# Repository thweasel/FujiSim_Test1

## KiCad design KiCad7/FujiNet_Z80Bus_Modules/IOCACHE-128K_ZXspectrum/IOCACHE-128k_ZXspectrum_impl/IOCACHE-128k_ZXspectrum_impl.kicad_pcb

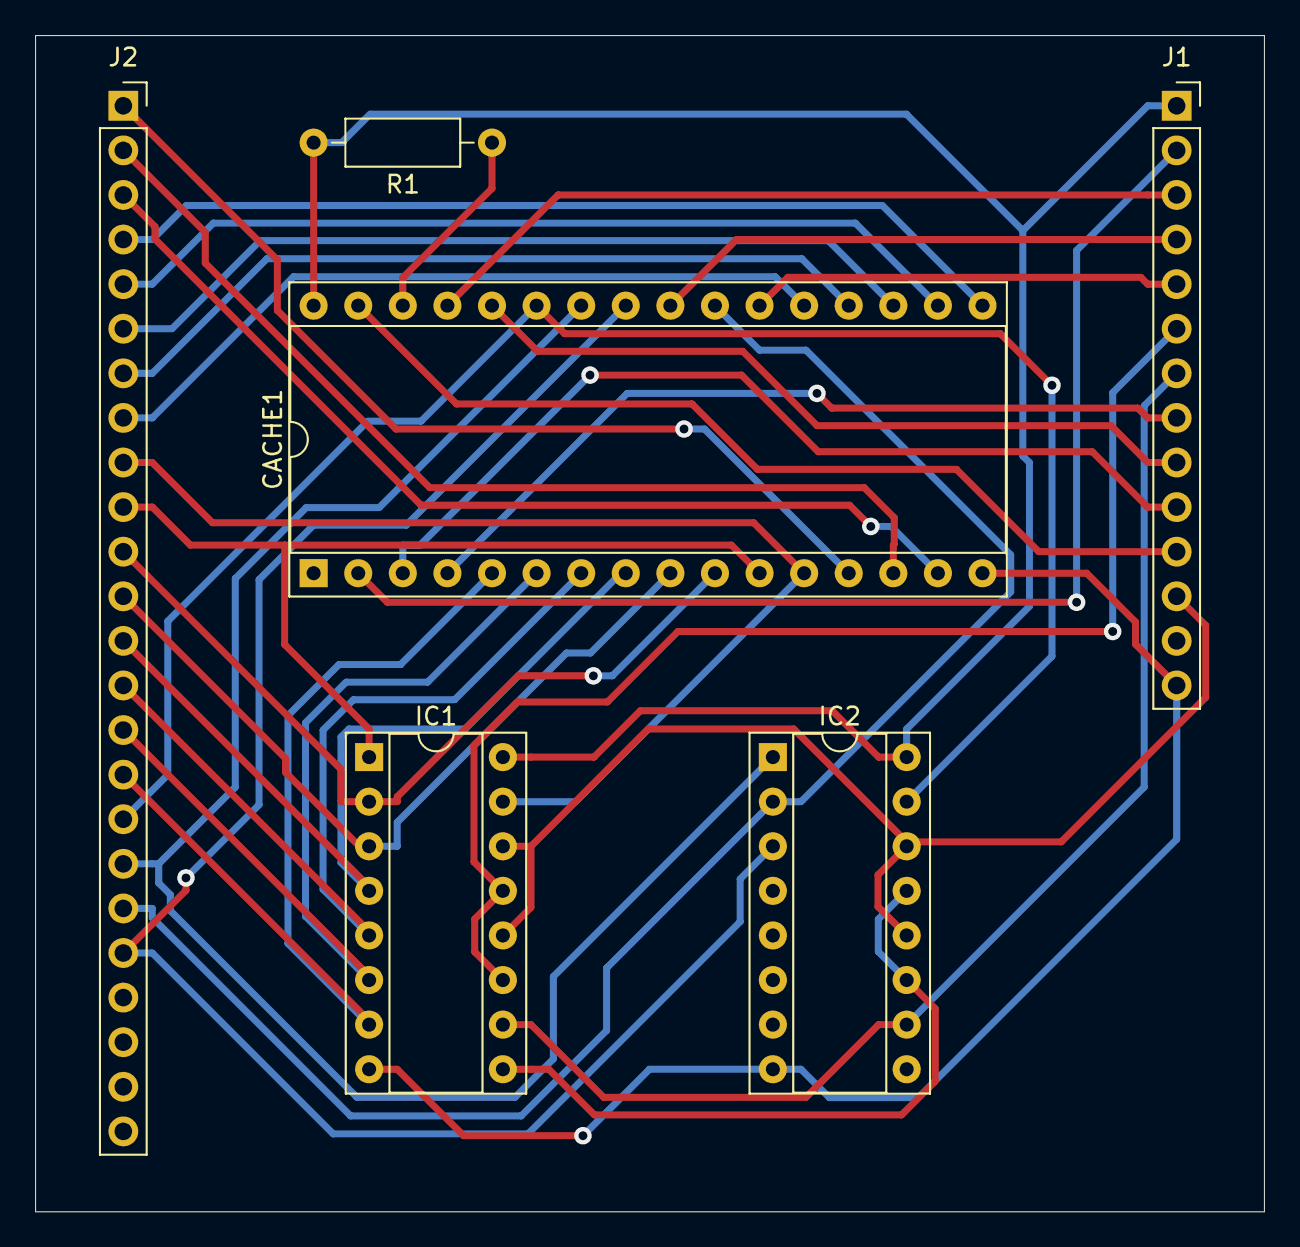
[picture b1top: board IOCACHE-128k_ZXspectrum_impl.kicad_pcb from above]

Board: 2 copper layers, 70.0 x 67.0 mm, 6 parts (0 on the bottom side), 35 nets.

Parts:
CACHE1: AS6C1008-55PCN; DIP-32_W15.24mm_Socket
IC1, IC2: 74HC590N; DIP-16_W7.62mm_Socket
J1: Conn_01x14_Socket; PinSocket_1x14_P2.54mm_Vertical
J2: Conn_01x24_Socket; PinSocket_1x24_P2.54mm_Vertical
R1: 10K; R_Axial_DIN0207_L6.3mm_D2.5mm_P10.16mm_Horizontal

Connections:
+5V: CACHE1.32 (VCC), IC1.16 (VCC), IC2.16 (VCC), J1.1, R1.2
/IOCACHE-128K_ZXspectrum/CACHE_CE2: CACHE1.30 (CE2#), R1.1
/IOCACHE-128K_ZXspectrum/CACHE_CONTROL.A16: CACHE1.2 (A16), J1.2
/IOCACHE-128K_ZXspectrum/CACHE_CONTROL.CS: CACHE1.22 (CE#), J1.5
/IOCACHE-128K_ZXspectrum/CACHE_CONTROL.DATASTATUS+PERM_Z80_IORQ: IC1.11 (CPC), IC1.13 (CPR), J1.6
/IOCACHE-128K_ZXspectrum/CACHE_CONTROL.OE: CACHE1.24 (OE#), J1.4
/IOCACHE-128K_ZXspectrum/CACHE_CONTROL.WE: CACHE1.29 (WE#), J1.3
/IOCACHE-128K_ZXspectrum/CACHE_DATASTATUS: IC1.12 (~CE), IC1.14 (~OE), IC2.12 (~CE), IC2.14 (~OE), J1.12
/IOCACHE-128K_ZXspectrum/CACHE_SEL_0: CACHE1.4 (A12), J1.8
/IOCACHE-128K_ZXspectrum/CACHE_SEL_1: CACHE1.28 (A13), J1.9
/IOCACHE-128K_ZXspectrum/CACHE_SEL_2: CACHE1.3 (A14), J1.10
/IOCACHE-128K_ZXspectrum/CACHE_SEL_3: CACHE1.31 (A15), J1.11
/IOCACHE-128K_ZXspectrum/LOCAL_A0: CACHE1.12 (A0), IC1.15 (Q0), J2.9
/IOCACHE-128K_ZXspectrum/LOCAL_A1: CACHE1.11 (A1), IC1.1 (Q1), J2.10
/IOCACHE-128K_ZXspectrum/LOCAL_A2: CACHE1.10 (A2), IC1.2 (Q2), J2.11
/IOCACHE-128K_ZXspectrum/LOCAL_A3: CACHE1.9 (A3), IC1.3 (Q3), J2.12
/IOCACHE-128K_ZXspectrum/LOCAL_A4: CACHE1.8 (A4), IC1.4 (Q4), J2.13
/IOCACHE-128K_ZXspectrum/LOCAL_A5: CACHE1.7 (A5), IC1.5 (Q5), J2.14
/IOCACHE-128K_ZXspectrum/LOCAL_A6: CACHE1.6 (A6), IC1.6 (Q6), J2.15
/IOCACHE-128K_ZXspectrum/LOCAL_A7: CACHE1.5 (A7), IC1.7 (Q7), J2.16
/IOCACHE-128K_ZXspectrum/LOCAL_A8: CACHE1.27 (A8), IC2.15 (Q0), J2.17
/IOCACHE-128K_ZXspectrum/LOCAL_A9: CACHE1.26 (A9), IC2.1 (Q1), J2.18
/IOCACHE-128K_ZXspectrum/LOCAL_A10: CACHE1.23 (A10), IC2.2 (Q2), J2.19
/IOCACHE-128K_ZXspectrum/LOCAL_A11: CACHE1.25 (A11), IC2.3 (Q3), J2.20
/IOCACHE-128K_ZXspectrum/LOCAL_D0: CACHE1.13 (DQ0), J2.1
/IOCACHE-128K_ZXspectrum/LOCAL_D1: CACHE1.14 (DQ1), J2.2
/IOCACHE-128K_ZXspectrum/LOCAL_D2: CACHE1.15 (DQ2), J2.3
/IOCACHE-128K_ZXspectrum/LOCAL_D3: CACHE1.17 (DQ3), J2.4
/IOCACHE-128K_ZXspectrum/LOCAL_D4: CACHE1.18 (DQ4), J2.5
/IOCACHE-128K_ZXspectrum/LOCAL_D5: CACHE1.19 (DQ5), J2.6
/IOCACHE-128K_ZXspectrum/LOCAL_D6: CACHE1.20 (DQ6), J2.7
/IOCACHE-128K_ZXspectrum/LOCAL_D7: CACHE1.21 (DQ7), J2.8
/IOCACHE-128K_ZXspectrum/Z80_HARDLOCK: IC1.10 (~MRC), IC2.10 (~MRC), J1.7
GND: CACHE1.16 (VSS), IC1.8 (GND), IC2.8 (GND), J1.14
unnamed: IC1.9 (~RCO), IC2.11 (CPC), IC2.13 (CPR)

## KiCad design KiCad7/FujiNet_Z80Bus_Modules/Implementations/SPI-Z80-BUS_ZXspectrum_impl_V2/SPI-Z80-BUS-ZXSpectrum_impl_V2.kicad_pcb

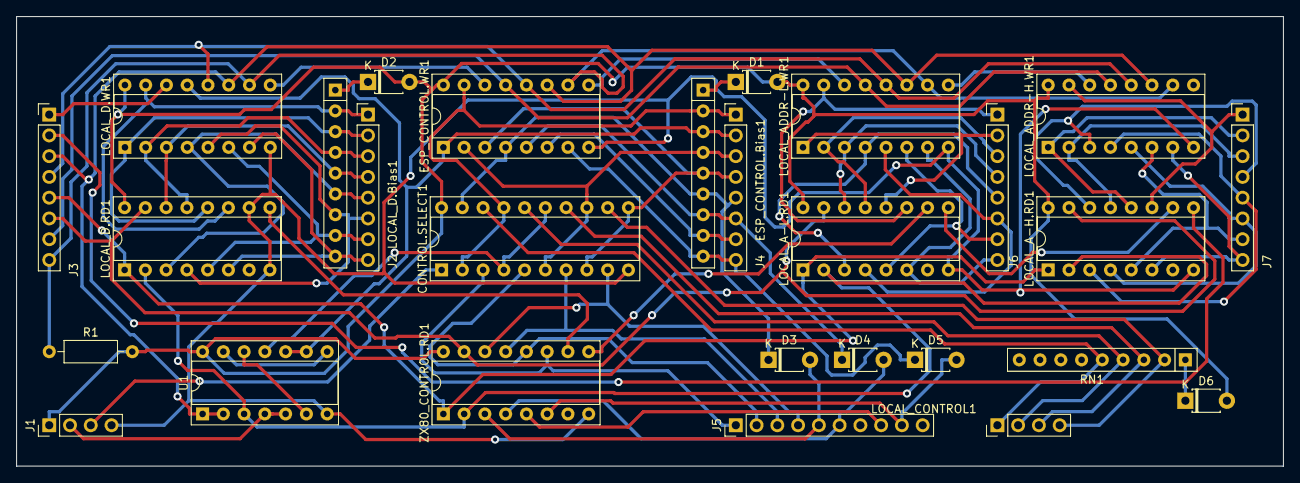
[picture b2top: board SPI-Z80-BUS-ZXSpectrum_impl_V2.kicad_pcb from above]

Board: 2 copper layers, 155.0 x 55.0 mm, 28 parts (0 on the bottom side), 69 nets.

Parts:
CONTROL.SELECT1: 74HC244N; DIP-20_W7.62mm_Socket
D1, D2, D3, D4, D5, D6: 1N4148; D_T-1_P5.08mm_Horizontal
ESP_CONTROL.Bias1: 4609M-101-103LF; R_Array_SIP9
ESP_CONTROL.WR1: 74595N; DIP-16_W7.62mm_Socket
J1: PinHeader_2.54mm; PinHeader_1x04_P2.54mm_Vertical
J2: LOCAL_D; PinHeader_1x08_P2.54mm_Vertical
J3: ESP_SPI_INT; PinHeader_1x08_P2.54mm_Vertical
J4: ESP_CONTROL; PinHeader_1x08_P2.54mm_Vertical
J5: Z80_CONTROL; PinHeader_1x10_P2.54mm_Vertical
J6: LOCAL_A-L; PinHeader_1x08_P2.54mm_Vertical
J7: LOCAL_A-H; PinHeader_1x08_P2.54mm_Vertical
LOCAL_A-H.RD1: 74HC165N; DIP-16_W7.62mm_Socket
LOCAL_A-L.RD1: 74HC165N; DIP-16_W7.62mm_Socket
LOCAL_ADDR-H.WR1: 74595N; DIP-16_W7.62mm_Socket
LOCAL_ADDR-L.WR1: 74595N; DIP-16_W7.62mm_Socket
LOCAL_CONTROL1: LOCAL_CONTROL; PinHeader_1x04_P2.54mm_Vertical
LOCAL_D.Bias1: 4609M-101-103LF; R_Array_SIP9
LOCAL_D.RD1: 74HC165N; DIP-16_W7.62mm_Socket
LOCAL_D.WR1: 74595N; DIP-16_W7.62mm_Socket
R1: 22K; R_Axial_DIN0207_L6.3mm_D2.5mm_P10.16mm_Horizontal
RN1: LOCAL_CONTROL.Bias; R_Array_SIP9
U1: 74HC00; DIP-14_W7.62mm_Socket
ZX80_CONTROL.RD1: 74HC165N; DIP-16_W7.62mm_Socket

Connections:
+5V: CONTROL.SELECT1.20 (VCC), D1.2 (A), D2.2 (A), D6.2 (A), ESP_CONTROL.WR1.16 (VCC), J1.1, LOCAL_A-H.RD1.16 (VCC), LOCAL_A-L.RD1.16 (VCC), LOCAL_ADDR-H.WR1.16 (VCC), LOCAL_ADDR-L.WR1.16 (VCC), LOCAL_D.RD1.16 (VCC), LOCAL_D.WR1.16 (VCC), R1.2, U1.14 (VCC), ZX80_CONTROL.RD1.16 (VCC)
/SPI-Z80-BUS/!ESP_HARDLOCK: CONTROL.SELECT1.1 (1OE), J1.3
/SPI-Z80-BUS/ESP_CONTROL.BUSRQ: CONTROL.SELECT1.19 (2OE), D3.1 (K), ESP_CONTROL.Bias1.6 (R5), ESP_CONTROL.WR1.4 (QE), J4.5
/SPI-Z80-BUS/ESP_CONTROL.IORQ: CONTROL.SELECT1.6 (1A2), CONTROL.SELECT1.13 (2A2), ESP_CONTROL.Bias1.4 (R3), ESP_CONTROL.WR1.2 (QC), J4.3
/SPI-Z80-BUS/ESP_CONTROL.MEMRQ: CONTROL.SELECT1.8 (1A3), CONTROL.SELECT1.11 (2A3), ESP_CONTROL.Bias1.5 (R4), ESP_CONTROL.WR1.3 (QD), J4.4
/SPI-Z80-BUS/ESP_CONTROL.NMI: D5.1 (K), ESP_CONTROL.Bias1.9 (R8), ESP_CONTROL.WR1.7 (QH), J4.8
/SPI-Z80-BUS/ESP_CONTROL.RD: CONTROL.SELECT1.2 (1A0), CONTROL.SELECT1.17 (2A0), ESP_CONTROL.Bias1.2 (R1), ESP_CONTROL.WR1.15 (QA), J4.1
/SPI-Z80-BUS/ESP_CONTROL.ROMCS: ESP_CONTROL.Bias1.8 (R7), ESP_CONTROL.WR1.6 (QG), J4.7
/SPI-Z80-BUS/ESP_CONTROL.WAIT: D4.1 (K), ESP_CONTROL.Bias1.7 (R6), ESP_CONTROL.WR1.5 (QF), J4.6
/SPI-Z80-BUS/ESP_CONTROL.WR: ESP_CONTROL.Bias1.3 (R2), ESP_CONTROL.WR1.1 (QB), J4.2, LOCAL_D.WR1.13 (~OE), U1.9, U1.10
/SPI-Z80-BUS/ESP_PULSE: J1.2, U1.4, U1.5
/SPI-Z80-BUS/ESP_SPI_INT.CE: J3.6, LOCAL_A-H.RD1.15 (~CE), LOCAL_A-L.RD1.15 (~CE), LOCAL_D.RD1.15 (~CE), ZX80_CONTROL.RD1.15 (~CE)
/SPI-Z80-BUS/ESP_SPI_INT.MISO: J3.2, LOCAL_A-H.RD1.9 (Q7)
/SPI-Z80-BUS/ESP_SPI_INT.MOSI: J3.1, LOCAL_D.WR1.14 (SER)
/SPI-Z80-BUS/ESP_SPI_INT.MR: ESP_CONTROL.WR1.10 (~SRCLR), J3.8, LOCAL_ADDR-H.WR1.10 (~SRCLR), LOCAL_ADDR-L.WR1.10 (~SRCLR), LOCAL_D.WR1.10 (~SRCLR), R1.1
/SPI-Z80-BUS/ESP_SPI_INT.OE: ESP_CONTROL.WR1.13 (~OE), J3.7, LOCAL_ADDR-H.WR1.13 (~OE), LOCAL_ADDR-L.WR1.13 (~OE)
/SPI-Z80-BUS/ESP_SPI_INT.PL: J3.5, LOCAL_A-H.RD1.1 (~PL), LOCAL_A-L.RD1.1 (~PL), LOCAL_D.RD1.1 (~PL), ZX80_CONTROL.RD1.1 (~PL)
/SPI-Z80-BUS/ESP_SPI_INT.SCK: ESP_CONTROL.WR1.11 (SRCLK), J3.3, LOCAL_ADDR-H.WR1.11 (SRCLK), LOCAL_ADDR-L.WR1.11 (SRCLK), LOCAL_D.WR1.11 (SRCLK), U1.1, U1.2
/SPI-Z80-BUS/ESP_SPI_INT.STC: ESP_CONTROL.WR1.12 (RCLK), J3.4, LOCAL_ADDR-H.WR1.12 (RCLK), LOCAL_ADDR-L.WR1.12 (RCLK), LOCAL_D.WR1.12 (RCLK)
/SPI-Z80-BUS/LOCAL_A0: J6.1, LOCAL_A-L.RD1.11 (D0), LOCAL_ADDR-L.WR1.15 (QA)
/SPI-Z80-BUS/LOCAL_A1: J6.2, LOCAL_A-L.RD1.12 (D1), LOCAL_ADDR-L.WR1.1 (QB)
/SPI-Z80-BUS/LOCAL_A2: J6.3, LOCAL_A-L.RD1.13 (D2), LOCAL_ADDR-L.WR1.2 (QC)
/SPI-Z80-BUS/LOCAL_A3: J6.4, LOCAL_A-L.RD1.14 (D3), LOCAL_ADDR-L.WR1.3 (QD)
/SPI-Z80-BUS/LOCAL_A4: J6.5, LOCAL_A-L.RD1.3 (D4), LOCAL_ADDR-L.WR1.4 (QE)
/SPI-Z80-BUS/LOCAL_A5: J6.6, LOCAL_A-L.RD1.4 (D5), LOCAL_ADDR-L.WR1.5 (QF)
/SPI-Z80-BUS/LOCAL_A6: J6.7, LOCAL_A-L.RD1.5 (D6), LOCAL_ADDR-L.WR1.6 (QG)
/SPI-Z80-BUS/LOCAL_A7: J6.8, LOCAL_A-L.RD1.6 (D7), LOCAL_ADDR-L.WR1.7 (QH)
/SPI-Z80-BUS/LOCAL_A8: J7.1, LOCAL_A-H.RD1.11 (D0), LOCAL_ADDR-H.WR1.15 (QA)
/SPI-Z80-BUS/LOCAL_A9: J7.2, LOCAL_A-H.RD1.12 (D1), LOCAL_ADDR-H.WR1.1 (QB)
/SPI-Z80-BUS/LOCAL_A10: J7.3, LOCAL_A-H.RD1.13 (D2), LOCAL_ADDR-H.WR1.2 (QC)
/SPI-Z80-BUS/LOCAL_A11: J7.4, LOCAL_A-H.RD1.14 (D3), LOCAL_ADDR-H.WR1.3 (QD)
/SPI-Z80-BUS/LOCAL_A12: J7.5, LOCAL_A-H.RD1.3 (D4), LOCAL_ADDR-H.WR1.4 (QE)
/SPI-Z80-BUS/LOCAL_A13: J7.6, LOCAL_A-H.RD1.4 (D5), LOCAL_ADDR-H.WR1.5 (QF)
/SPI-Z80-BUS/LOCAL_A14: J7.7, LOCAL_A-H.RD1.5 (D6), LOCAL_ADDR-H.WR1.6 (QG)
/SPI-Z80-BUS/LOCAL_A15: J7.8, LOCAL_A-H.RD1.6 (D7), LOCAL_ADDR-H.WR1.7 (QH)
/SPI-Z80-BUS/LOCAL_CONTROL.IORQ: CONTROL.SELECT1.14 (1Y2), LOCAL_CONTROL1.3, RN1.3 (R2)
/SPI-Z80-BUS/LOCAL_CONTROL.MEMRQ: CONTROL.SELECT1.12 (1Y3), LOCAL_CONTROL1.4, RN1.2 (R1)
/SPI-Z80-BUS/LOCAL_CONTROL.RD: CONTROL.SELECT1.18 (1Y0), LOCAL_CONTROL1.1, RN1.5 (R4)
/SPI-Z80-BUS/LOCAL_CONTROL.WR: CONTROL.SELECT1.16 (1Y1), LOCAL_CONTROL1.2, RN1.4 (R3)
/SPI-Z80-BUS/LOCAL_D0: J2.1, LOCAL_D.Bias1.2 (R1), LOCAL_D.RD1.11 (D0), LOCAL_D.WR1.15 (QA)
/SPI-Z80-BUS/LOCAL_D1: J2.2, LOCAL_D.Bias1.3 (R2), LOCAL_D.RD1.12 (D1), LOCAL_D.WR1.1 (QB)
/SPI-Z80-BUS/LOCAL_D2: J2.3, LOCAL_D.Bias1.4 (R3), LOCAL_D.RD1.13 (D2), LOCAL_D.WR1.2 (QC)
/SPI-Z80-BUS/LOCAL_D3: J2.4, LOCAL_D.Bias1.5 (R4), LOCAL_D.RD1.14 (D3), LOCAL_D.WR1.3 (QD)
/SPI-Z80-BUS/LOCAL_D4: J2.5, LOCAL_D.Bias1.6 (R5), LOCAL_D.RD1.3 (D4), LOCAL_D.WR1.4 (QE)
/SPI-Z80-BUS/LOCAL_D5: J2.6, LOCAL_D.Bias1.7 (R6), LOCAL_D.RD1.4 (D5), LOCAL_D.WR1.5 (QF)
/SPI-Z80-BUS/LOCAL_D6: J2.7, LOCAL_D.Bias1.8 (R7), LOCAL_D.RD1.5 (D6), LOCAL_D.WR1.6 (QG)
/SPI-Z80-BUS/LOCAL_D7: J2.8, LOCAL_D.Bias1.9 (R8), LOCAL_D.RD1.6 (D7), LOCAL_D.WR1.7 (QH)
/SPI-Z80-BUS/SPI-Z80-BUS_read/ESP_SPI_INT.SCK: LOCAL_A-H.RD1.2 (CP), LOCAL_A-L.RD1.2 (CP), LOCAL_D.RD1.2 (CP), U1.3, ZX80_CONTROL.RD1.2 (CP)
/SPI-Z80-BUS/Z80_CONTROL.BUSACK: J5.8, ZX80_CONTROL.RD1.5 (D6)
/SPI-Z80-BUS/Z80_CONTROL.BUSRQ: D3.2 (A), J5.5, ZX80_CONTROL.RD1.3 (D4)
/SPI-Z80-BUS/Z80_CONTROL.IORQ: CONTROL.SELECT1.7 (2Y2), J5.3, ZX80_CONTROL.RD1.13 (D2)
/SPI-Z80-BUS/Z80_CONTROL.MEMRQ: CONTROL.SELECT1.9 (2Y3), J5.4, ZX80_CONTROL.RD1.14 (D3)
/SPI-Z80-BUS/Z80_CONTROL.NMI: D5.2 (A), J5.9, ZX80_CONTROL.RD1.6 (D7)
/SPI-Z80-BUS/Z80_CONTROL.RD: CONTROL.SELECT1.3 (2Y0), J5.1, ZX80_CONTROL.RD1.11 (D0)
/SPI-Z80-BUS/Z80_CONTROL.WAIT: D4.2 (A), J5.6, ZX80_CONTROL.RD1.4 (D5)
/SPI-Z80-BUS/Z80_CONTROL.WR: CONTROL.SELECT1.5 (2Y1), J5.2, ZX80_CONTROL.RD1.12 (D1)
GND: CONTROL.SELECT1.10 (GND), ESP_CONTROL.WR1.8 (GND), J1.4, LOCAL_A-H.RD1.8 (GND), LOCAL_A-L.RD1.8 (GND), LOCAL_ADDR-H.WR1.8 (GND), LOCAL_ADDR-L.WR1.8 (GND), LOCAL_D.RD1.8 (GND), LOCAL_D.RD1.10 (DS), LOCAL_D.WR1.8 (GND), U1.7 (GND), ZX80_CONTROL.RD1.8 (GND)
unnamed: CONTROL.SELECT1.4 (1A1), CONTROL.SELECT1.15 (2A1), U1.11
unnamed: D1.1 (K), ESP_CONTROL.Bias1.1 (common)
unnamed: D2.1 (K), LOCAL_D.Bias1.1 (common)
unnamed: D6.1 (K), RN1.1 (common)
unnamed: ESP_CONTROL.WR1.9 (QH'), LOCAL_ADDR-L.WR1.14 (SER)
unnamed: ESP_CONTROL.WR1.14 (SER), LOCAL_D.WR1.9 (QH')
unnamed: LOCAL_A-H.RD1.10 (DS), LOCAL_A-L.RD1.9 (Q7)
unnamed: LOCAL_A-L.RD1.10 (DS), ZX80_CONTROL.RD1.9 (Q7)
unnamed: LOCAL_ADDR-H.WR1.14 (SER), LOCAL_ADDR-L.WR1.9 (QH')
unnamed: LOCAL_D.RD1.9 (Q7), ZX80_CONTROL.RD1.10 (DS)
unnamed: U1.6, U1.12
unnamed: U1.8, U1.13

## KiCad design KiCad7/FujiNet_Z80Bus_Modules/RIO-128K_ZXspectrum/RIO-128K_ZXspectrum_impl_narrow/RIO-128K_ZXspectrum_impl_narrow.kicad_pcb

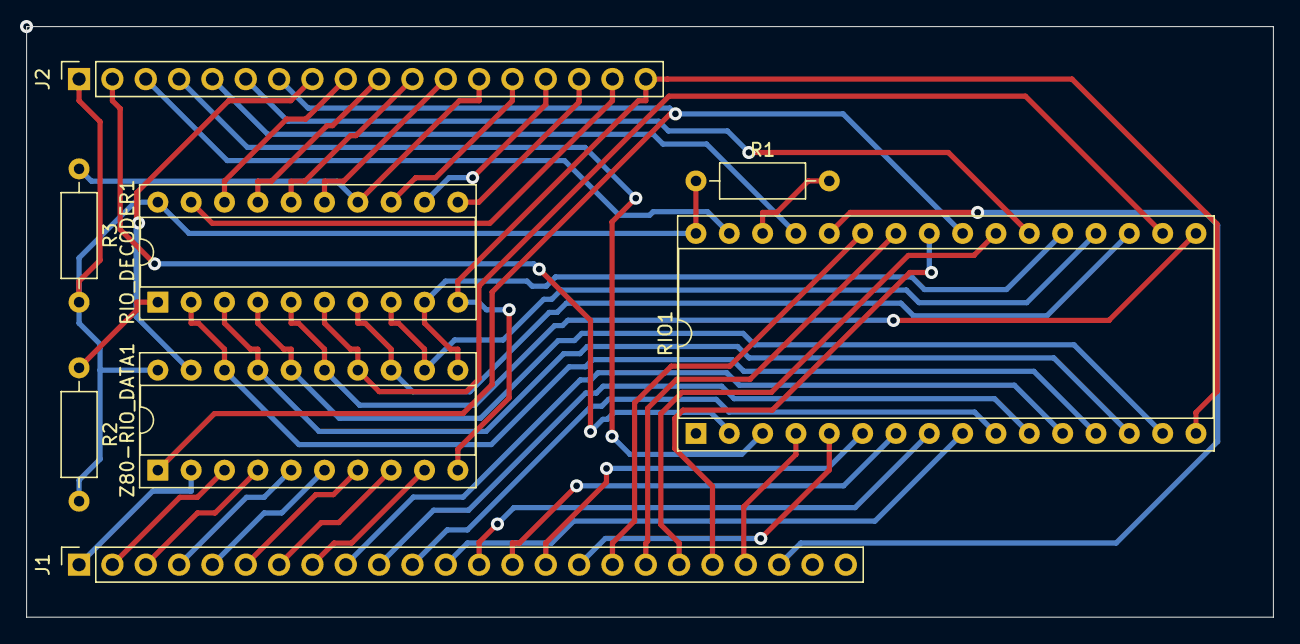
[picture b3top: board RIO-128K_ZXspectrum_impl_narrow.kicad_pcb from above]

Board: 2 copper layers, 95.0 x 45.0 mm, 8 parts (0 on the bottom side), 50 nets.

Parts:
J1: Conn_01x24_Socket; PinSocket_1x24_P2.54mm_Vertical
J2: Conn_01x18_Socket; PinSocket_1x18_P2.54mm_Vertical
R1, R2, R3: 10K; R_Axial_DIN0207_L6.3mm_D2.5mm_P10.16mm_Horizontal
RIO1: AS6C1008-55PCN; DIP-32_W15.24mm_Socket
RIO_DECODER1: 74HC245N; DIP-20_W7.62mm_Socket
Z80-RIO_DATA1: 74HC245N; DIP-20_W7.62mm_Socket

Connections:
+5V: J2.1, R1.1, R2.2, R3.2, RIO1.32 (VCC), RIO_DECODER1.20 (VCC), Z80-RIO_DATA1.20 (VCC)
/RIO-128K_ZXspectrum/CACHE_DATASTATUS: J2.13, R3.1, RIO_DECODER1.14 (B4)
/RIO-128K_ZXspectrum/CACHE_SEL_0: J2.9, RIO_DECODER1.18 (B0)
/RIO-128K_ZXspectrum/CACHE_SEL_1: J2.10, RIO_DECODER1.17 (B1)
/RIO-128K_ZXspectrum/CACHE_SEL_2: J2.11, RIO_DECODER1.16 (B2)
/RIO-128K_ZXspectrum/CACHE_SEL_3: J2.12, RIO_DECODER1.15 (B3)
/RIO-128K_ZXspectrum/PERM_Z80_IORQ: J2.17, RIO_DECODER1.19 (CE)
/RIO-128K_ZXspectrum/RIO_CE2: R1.2, RIO1.30 (CE2#)
/RIO-128K_ZXspectrum/RIO_CONTROL.A14: J2.4, RIO1.3 (A14)
/RIO-128K_ZXspectrum/RIO_CONTROL.A15: J2.3, RIO1.31 (A15)
/RIO-128K_ZXspectrum/RIO_CONTROL.A16: J2.2, RIO1.2 (A16)
/RIO-128K_ZXspectrum/RIO_CONTROL.CE: J2.6, RIO1.22 (CE#)
/RIO-128K_ZXspectrum/RIO_CONTROL.OE: J2.7, RIO1.24 (OE#), Z80-RIO_DATA1.1 (A->B)
/RIO-128K_ZXspectrum/RIO_CONTROL.ROM_RDY: J2.8, Z80-RIO_DATA1.19 (CE)
/RIO-128K_ZXspectrum/RIO_CONTROL.WE: J2.5, RIO1.29 (WE#)
/RIO-128K_ZXspectrum/ROM_D0: RIO1.13 (DQ0), RIO_DECODER1.2 (A0), Z80-RIO_DATA1.18 (B0)
/RIO-128K_ZXspectrum/ROM_D1: RIO1.14 (DQ1), RIO_DECODER1.3 (A1), Z80-RIO_DATA1.17 (B1)
/RIO-128K_ZXspectrum/ROM_D2: RIO1.15 (DQ2), RIO_DECODER1.4 (A2), Z80-RIO_DATA1.16 (B2)
/RIO-128K_ZXspectrum/ROM_D3: RIO1.17 (DQ3), RIO_DECODER1.5 (A3), Z80-RIO_DATA1.15 (B3)
/RIO-128K_ZXspectrum/ROM_D4: RIO1.18 (DQ4), RIO_DECODER1.6 (A4), Z80-RIO_DATA1.14 (B4)
/RIO-128K_ZXspectrum/ROM_D5: RIO1.19 (DQ5), RIO_DECODER1.7 (A5), Z80-RIO_DATA1.13 (B5)
/RIO-128K_ZXspectrum/ROM_D6: RIO1.20 (DQ6), RIO_DECODER1.8 (A6), Z80-RIO_DATA1.12 (B6)
/RIO-128K_ZXspectrum/ROM_D7: RIO1.21 (DQ7), RIO_DECODER1.9 (A7), Z80-RIO_DATA1.11 (B7)
/RIO-128K_ZXspectrum/WAIT_IO: J2.14, RIO_DECODER1.13 (B5)
/RIO-128K_ZXspectrum/Z80_A0: J1.9, RIO1.12 (A0)
/RIO-128K_ZXspectrum/Z80_A1: J1.10, RIO1.11 (A1)
/RIO-128K_ZXspectrum/Z80_A2: J1.11, RIO1.10 (A2)
/RIO-128K_ZXspectrum/Z80_A3: J1.12, RIO1.9 (A3)
/RIO-128K_ZXspectrum/Z80_A4: J1.13, RIO1.8 (A4)
/RIO-128K_ZXspectrum/Z80_A5: J1.14, RIO1.7 (A5)
/RIO-128K_ZXspectrum/Z80_A6: J1.15, RIO1.6 (A6)
/RIO-128K_ZXspectrum/Z80_A7: J1.16, RIO1.5 (A7)
/RIO-128K_ZXspectrum/Z80_A8: J1.17, RIO1.27 (A8)
/RIO-128K_ZXspectrum/Z80_A9: J1.18, RIO1.26 (A9)
/RIO-128K_ZXspectrum/Z80_A10: J1.19, RIO1.23 (A10)
/RIO-128K_ZXspectrum/Z80_A11: J1.20, RIO1.25 (A11)
/RIO-128K_ZXspectrum/Z80_A12: J1.21, RIO1.4 (A12)
/RIO-128K_ZXspectrum/Z80_A13: J1.22, RIO1.28 (A13)
/RIO-128K_ZXspectrum/Z80_D0: J1.1, Z80-RIO_DATA1.2 (A0)
/RIO-128K_ZXspectrum/Z80_D1: J1.2, Z80-RIO_DATA1.3 (A1)
/RIO-128K_ZXspectrum/Z80_D2: J1.3, Z80-RIO_DATA1.4 (A2)
/RIO-128K_ZXspectrum/Z80_D3: J1.4, Z80-RIO_DATA1.5 (A3)
/RIO-128K_ZXspectrum/Z80_D4: J1.5, Z80-RIO_DATA1.6 (A4)
/RIO-128K_ZXspectrum/Z80_D5: J1.6, Z80-RIO_DATA1.7 (A5)
/RIO-128K_ZXspectrum/Z80_D6: J1.7, Z80-RIO_DATA1.8 (A6)
/RIO-128K_ZXspectrum/Z80_D7: J1.8, Z80-RIO_DATA1.9 (A7)
/RIO-128K_ZXspectrum/Z80_HARDLOCK_RESET: J2.15, RIO_DECODER1.12 (B6)
/RIO-128K_ZXspectrum/Z80_HARDLOCK_SET: J2.16, RIO_DECODER1.11 (B7)
GND: J2.18, RIO1.16 (VSS), RIO_DECODER1.10 (GND), Z80-RIO_DATA1.10 (GND)
unnamed: R2.1, RIO_DECODER1.1 (A->B)

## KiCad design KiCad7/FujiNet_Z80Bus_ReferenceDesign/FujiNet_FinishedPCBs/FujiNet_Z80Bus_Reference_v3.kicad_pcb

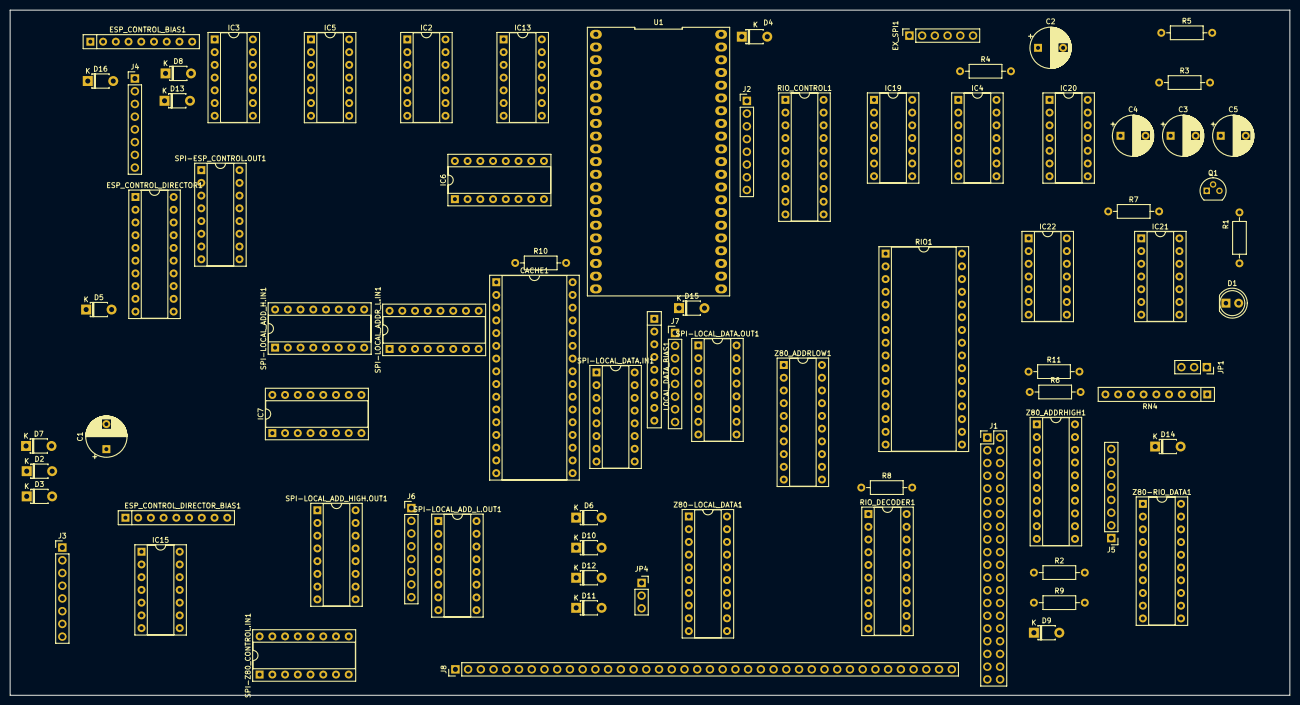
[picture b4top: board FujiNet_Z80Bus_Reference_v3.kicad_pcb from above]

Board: 2 copper layers, 255.4 x 136.7 mm, 78 parts (0 on the bottom side), 169 nets, no tracks yet.

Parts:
C1, C2: 10UF; CP_Radial_D8.0mm_P5.00mm
C3: 10 uf; CP_Radial_D8.0mm_P5.00mm
C4, C5: .1 uf; CP_Radial_D8.0mm_P5.00mm
CACHE1: AS6C1008-55PCN; DIP-32_W15.24mm_Socket
D1: POWER_LED; LED_D5.0mm
D2, D3, D4, D5, D6, D7, D8, D9, D10, D11, D12, D13, D14, D15, D16: 1N4148; D_T-1_P5.08mm_Horizontal
ESP_CONTROL_BIAS1: 4609M-101-103LF; R_Array_SIP9
ESP_CONTROL_DIRECTOR1: 74244N; DIP-20_W7.62mm_Socket
ESP_CONTROL_DIRECTOR_BIAS1: 4609M-101-103LF; R_Array_SIP9
EX_SPI1: PINHD-1X6; PinSocket_1x06_P2.54mm_Vertical
IC2: 7404N; DIP-14_W7.62mm_Socket
IC3: 7474N; DIP-14_W7.62mm_Socket
IC4, IC13, IC19, IC21, IC22: 7432N; DIP-14_W7.62mm_Socket
IC5, IC15, IC20: 7408N; DIP-14_W7.62mm_Socket
IC6, IC7: 74590N; DIP-16_W7.62mm_Socket
J1: HOST SYSTEM HEADER; PinHeader_2x20_P2.54mm_Vertical
J2: DIAG-ESP_SPI; PinHeader_1x08_P2.54mm_Vertical
J3: DIAG-Z80_CONTROL; PinHeader_1x08_P2.54mm_Vertical
J4: DIAG-ESP_CONTROL; PinHeader_1x08_P2.54mm_Vertical
J5: DIAG-LOCAL_ADD_HIGH; PinHeader_1x08_P2.54mm_Vertical
J6: DIAG-LOCAL_ADD_LOW; PinHeader_1x08_P2.54mm_Vertical
J7: DIAG-LOCAL_DATA; PinHeader_1x08_P2.54mm_Vertical
J8: DIAG-HOST_SYSTEM_BUS; PinHeader_1x40_P2.54mm_Vertical
JP1: PINHD-ADDR_FILTER; PinSocket_1x03_P2.54mm_Vertical
JP4: PINHD-POWER/RESET; PinSocket_1x03_P2.54mm_Vertical
LOCAL_DATA_BIAS1: 4609M-101-103LF; R_Array_SIP9
Q1: 2N2222 (BC337); TO-92
R1, R2, R7: 1K; R_Axial_DIN0207_L6.3mm_D2.5mm_P10.16mm_Horizontal
R3, R4, R5, R6: 22K; R_Axial_DIN0207_L6.3mm_D2.5mm_P10.16mm_Horizontal
R8, R9, R10, R11: 10K; R_Axial_DIN0207_L6.3mm_D2.5mm_P10.16mm_Horizontal
RIO1: AS6C1008-55PCN; DIP-32_W15.24mm_Socket
RIO_CONTROL1: 74244N; DIP-20_W7.62mm_Socket
RIO_DECODER1: 74245N; DIP-20_W7.62mm_Socket
RN4: 4609M-101-103LF; R_Array_SIP9
SPI-ESP_CONTROL.OUT1: 74595N; DIP-16_W7.62mm_Socket
SPI-LOCAL_ADDR_L.IN1: 74165N; DIP-16_W7.62mm_Socket
SPI-LOCAL_ADD_H.IN1: 74165N; DIP-16_W7.62mm_Socket
SPI-LOCAL_ADD_HIGH.OUT1: 74595N; DIP-16_W7.62mm_Socket
SPI-LOCAL_ADD_L.OUT1: 74595N; DIP-16_W7.62mm_Socket
SPI-LOCAL_DATA.IN1: 74165N; DIP-16_W7.62mm_Socket
SPI-LOCAL_DATA.OUT1: 74595N; DIP-16_W7.62mm_Socket
SPI-Z80_CONTROL.IN1: 74165N; DIP-16_W7.62mm_Socket
U1: FREENOVE_ESP32-WROVER-DEV
Z80-LOCAL_DATA1, Z80-RIO_DATA1, Z80_ADDRHIGH1, Z80_ADDRLOW1: 74245N; DIP-20_W7.62mm_Socket

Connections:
+5V: C3.1, C4.1, C5.1, CACHE1.32 (VCC), D5.2 (A), D14.2 (A), D15.2 (A), D16.2 (A), EX_SPI1.5, JP4.3, R1.2, R3.1, R4.1, R6.1, R7.2, R8.2, R9.2, R10.2, R11.1, RIO1.32 (VCC), U1.19 (+5v), U1.20 (+5V)
/!CACHE_DATASTATUS: IC21.2 (I1), Q1.1 (C), R7.1
/CACHE/CACHE_A16: CACHE1.2 (A16), IC15.3 (O)
/CACHE/CACHE_CE2: CACHE1.30 (CE2), R10.1
/CACHE/CACHE_CS: CACHE1.22 (~CE), IC15.11 (O)
/CACHE/CACHE_DATASTATUS+PERM_Z80_IORQ: IC6.11 (CLK), IC6.13 (RCK), IC13.6 (O)
/CACHE/CACHE_OE: CACHE1.24 (~OE), IC15.8 (O)
/CACHE/CACHE_WE: CACHE1.29 (~WE), IC15.6 (O)
/CACHE/LOCAL_A0: CACHE1.12 (A0), IC6.15 (QA), J6.1, SPI-LOCAL_ADDR_L.IN1.11 (A), SPI-LOCAL_ADD_L.OUT1.15 (QA), Z80_ADDRLOW1.18 (B1)
/CACHE/LOCAL_A1: CACHE1.11 (A1), IC6.1 (QB), J6.2, SPI-LOCAL_ADDR_L.IN1.12 (B), SPI-LOCAL_ADD_L.OUT1.1 (QB), Z80_ADDRLOW1.17 (B2)
/CACHE/LOCAL_A2: CACHE1.10 (A2), IC6.2 (QC), J6.3, SPI-LOCAL_ADDR_L.IN1.13 (C), SPI-LOCAL_ADD_L.OUT1.2 (QC), Z80_ADDRLOW1.16 (B3)
/CACHE/LOCAL_A3: CACHE1.9 (A3), IC6.3 (QD), J6.4, SPI-LOCAL_ADDR_L.IN1.14 (D), SPI-LOCAL_ADD_L.OUT1.3 (QD), Z80_ADDRLOW1.15 (B4)
/CACHE/LOCAL_A4: CACHE1.8 (A4), IC6.4 (QE), J6.5, SPI-LOCAL_ADDR_L.IN1.3 (E), SPI-LOCAL_ADD_L.OUT1.4 (QE), Z80_ADDRLOW1.14 (B5)
/CACHE/LOCAL_A5: CACHE1.7 (A5), IC6.5 (QF), J6.6, SPI-LOCAL_ADDR_L.IN1.4 (F), SPI-LOCAL_ADD_L.OUT1.5 (QF), Z80_ADDRLOW1.13 (B6)
/CACHE/LOCAL_A6: CACHE1.6 (A6), IC6.6 (QG), J6.7, SPI-LOCAL_ADDR_L.IN1.5 (G), SPI-LOCAL_ADD_L.OUT1.6 (QG), Z80_ADDRLOW1.12 (B7)
/CACHE/LOCAL_A7: CACHE1.5 (A7), IC6.7 (QH), J6.8, SPI-LOCAL_ADDR_L.IN1.6 (H), SPI-LOCAL_ADD_L.OUT1.7 (QH), Z80_ADDRLOW1.11 (B8)
/CACHE/LOCAL_A8: CACHE1.27 (A8), IC7.15 (QA), J5.1, SPI-LOCAL_ADD_H.IN1.11 (A), SPI-LOCAL_ADD_HIGH.OUT1.15 (QA), Z80_ADDRHIGH1.18 (B1)
/CACHE/LOCAL_A9: CACHE1.26 (A9), IC7.1 (QB), J5.2, SPI-LOCAL_ADD_H.IN1.12 (B), SPI-LOCAL_ADD_HIGH.OUT1.1 (QB), Z80_ADDRHIGH1.17 (B2)
/CACHE/LOCAL_A10: CACHE1.23 (A10), IC7.2 (QC), J5.3, SPI-LOCAL_ADD_H.IN1.13 (C), SPI-LOCAL_ADD_HIGH.OUT1.2 (QC), Z80_ADDRHIGH1.16 (B3)
/CACHE/LOCAL_A11: CACHE1.25 (A11), IC7.3 (QD), J5.4, SPI-LOCAL_ADD_H.IN1.14 (D), SPI-LOCAL_ADD_HIGH.OUT1.3 (QD), Z80_ADDRHIGH1.15 (B4)
/CACHE/LOCAL_A12: J5.5, SPI-LOCAL_ADD_H.IN1.3 (E), SPI-LOCAL_ADD_HIGH.OUT1.4 (QE), Z80_ADDRHIGH1.14 (B5)
/CACHE/LOCAL_A13: J5.6, SPI-LOCAL_ADD_H.IN1.4 (F), SPI-LOCAL_ADD_HIGH.OUT1.5 (QF), Z80_ADDRHIGH1.13 (B6)
/CACHE/LOCAL_A14: J5.7, SPI-LOCAL_ADD_H.IN1.5 (G), SPI-LOCAL_ADD_HIGH.OUT1.6 (QG), Z80_ADDRHIGH1.12 (B7)
/CACHE/LOCAL_A15: J5.8, SPI-LOCAL_ADD_H.IN1.6 (H), SPI-LOCAL_ADD_HIGH.OUT1.7 (QH), Z80_ADDRHIGH1.11 (B8)
/CACHE/LOCAL_CONTROL.IORQ: ESP_CONTROL_DIRECTOR1.14 (Y3), ESP_CONTROL_DIRECTOR_BIAS1.4, IC15.2 (I1)
/CACHE/LOCAL_CONTROL.MEMRQ: ESP_CONTROL_DIRECTOR1.12 (Y4), ESP_CONTROL_DIRECTOR_BIAS1.5, IC15.13 (I1)
/CACHE/LOCAL_CONTROL.RD: ESP_CONTROL_DIRECTOR1.18 (Y1), ESP_CONTROL_DIRECTOR_BIAS1.2, IC15.10 (I1)
/CACHE/LOCAL_CONTROL.WR: ESP_CONTROL_DIRECTOR1.16 (Y2), ESP_CONTROL_DIRECTOR_BIAS1.3, IC15.5 (I1)
/CACHE/LOCAL_D0: CACHE1.13 (DQ0), J7.1, LOCAL_DATA_BIAS1.2, SPI-LOCAL_DATA.IN1.11 (A), SPI-LOCAL_DATA.OUT1.15 (QA), Z80-LOCAL_DATA1.18 (B1)
/CACHE/LOCAL_D1: CACHE1.14 (DQ1), J7.2, LOCAL_DATA_BIAS1.3, SPI-LOCAL_DATA.IN1.12 (B), SPI-LOCAL_DATA.OUT1.1 (QB), Z80-LOCAL_DATA1.17 (B2)
/CACHE/LOCAL_D2: CACHE1.15 (DQ2), J7.3, LOCAL_DATA_BIAS1.4, SPI-LOCAL_DATA.IN1.13 (C), SPI-LOCAL_DATA.OUT1.2 (QC), Z80-LOCAL_DATA1.16 (B3)
/CACHE/LOCAL_D3: CACHE1.17 (DQ3), J7.4, LOCAL_DATA_BIAS1.5, SPI-LOCAL_DATA.IN1.14 (D), SPI-LOCAL_DATA.OUT1.3 (QD), Z80-LOCAL_DATA1.15 (B4)
/CACHE/LOCAL_D4: CACHE1.18 (DQ4), J7.5, LOCAL_DATA_BIAS1.6, SPI-LOCAL_DATA.IN1.3 (E), SPI-LOCAL_DATA.OUT1.4 (QE), Z80-LOCAL_DATA1.14 (B5)
/CACHE/LOCAL_D5: CACHE1.19 (DQ5), J7.6, LOCAL_DATA_BIAS1.7, SPI-LOCAL_DATA.IN1.4 (F), SPI-LOCAL_DATA.OUT1.5 (QF), Z80-LOCAL_DATA1.13 (B6)
/CACHE/LOCAL_D6: CACHE1.20 (DQ6), J7.7, LOCAL_DATA_BIAS1.8, SPI-LOCAL_DATA.IN1.5 (G), SPI-LOCAL_DATA.OUT1.6 (QG), Z80-LOCAL_DATA1.12 (B7)
/CACHE/LOCAL_D7: CACHE1.21 (DQ7), J7.8, LOCAL_DATA_BIAS1.9, SPI-LOCAL_DATA.IN1.6 (H), SPI-LOCAL_DATA.OUT1.7 (QH), Z80-LOCAL_DATA1.11 (B8)
/CACHE_DATASTATUS: IC6.12 (CCKEN), IC6.14 (G), IC7.12 (CCKEN), IC7.14 (G), IC13.5 (I1), IC15.1 (I0), R2.1, R9.1, RIO_DECODER1.14 (B5)
/CACHE_SEL_0: CACHE1.4 (A12), RIO_DECODER1.18 (B1)
/CACHE_SEL_1: CACHE1.28 (A13), RIO_DECODER1.17 (B2)
/CACHE_SEL_2: CACHE1.3 (A14), RIO_DECODER1.16 (B3)
/CACHE_SEL_3: CACHE1.31 (A15), RIO_DECODER1.15 (B4)
/CORE/!ESP_HARDLOCK: ESP_CONTROL_DIRECTOR1.1 (G), IC2.2 (O)
/CORE/CLR_Z80_HARDLOCK: IC3.1 (CLR), IC5.3 (O)
/CORE/ESP_CONTROL.BUSRQ: D2.1 (K), D3.1 (K), D7.1 (K), ESP_CONTROL_BIAS1.6, ESP_CONTROL_DIRECTOR1.19 (G), IC4.10 (I1), J4.5, SPI-ESP_CONTROL.OUT1.4 (QE)
/CORE/ESP_CONTROL.IORQ: ESP_CONTROL_BIAS1.4, ESP_CONTROL_DIRECTOR1.6 (A3), ESP_CONTROL_DIRECTOR1.15 (A3), IC5.5 (I1), J4.3, SPI-ESP_CONTROL.OUT1.2 (QC)
/CORE/ESP_CONTROL.MEMRQ: ESP_CONTROL_BIAS1.5, ESP_CONTROL_DIRECTOR1.8 (A4), ESP_CONTROL_DIRECTOR1.17 (A4), IC5.4 (I0), IC22.5 (I1), J4.4, SPI-ESP_CONTROL.OUT1.3 (QD)
/CORE/ESP_CONTROL.NMI: D10.1 (K), ESP_CONTROL_BIAS1.9, J4.8, SPI-ESP_CONTROL.OUT1.7 (QH)
/CORE/ESP_CONTROL.RD: ESP_CONTROL_BIAS1.2, ESP_CONTROL_DIRECTOR1.2 (A1), ESP_CONTROL_DIRECTOR1.11 (A1), J4.1, SPI-ESP_CONTROL.OUT1.15 (QA)
/CORE/ESP_CONTROL.ROMCS: D9.1 (K), ESP_CONTROL_BIAS1.8, IC19.9 (I0), J4.7, SPI-ESP_CONTROL.OUT1.6 (QG)
/CORE/ESP_CONTROL.WAIT: D8.1 (K), ESP_CONTROL_BIAS1.7, J4.6, SPI-ESP_CONTROL.OUT1.5 (QF)
/CORE/ESP_CONTROL.WR: ESP_CONTROL_BIAS1.3, IC13.13 (I1), IC21.9 (I0), J2.4, J4.2, SPI-ESP_CONTROL.OUT1.1 (QB), SPI-LOCAL_DATA.OUT1.13 (G)
/CORE/ESP_HARDLOCK: IC2.1 (I), IC13.2 (I1), IC13.9 (I0), U1.26 (GPIO2)
/CORE/ESP_INT: D6.2 (A), D11.2 (A), D12.2 (A), R3.2, R5.1, U1.3 (GPIO36)
/CORE/ESP_PULSE: IC13.12 (I0), U1.11 (GPIO27)
/CORE/ESP_SPI_INT.CE: J2.7, SPI-LOCAL_ADDR_L.IN1.15 (INH), SPI-LOCAL_ADD_H.IN1.15 (INH), SPI-LOCAL_DATA.IN1.15 (INH), SPI-Z80_CONTROL.IN1.15 (INH), U1.31 (GPIO5)
/CORE/ESP_SPI_INT.MISO: J2.2, SPI-LOCAL_ADD_H.IN1.9 (QH), U1.33 (GPIO19)
/CORE/ESP_SPI_INT.MOSI: J2.1, SPI-LOCAL_DATA.OUT1.14 (SER), U1.39 (GPIO23)
/CORE/ESP_SPI_INT.MR: R6.2, SPI-ESP_CONTROL.OUT1.10 (SCL), SPI-LOCAL_ADD_HIGH.OUT1.10 (SCL), SPI-LOCAL_ADD_L.OUT1.10 (SCL), SPI-LOCAL_DATA.OUT1.10 (SCL)
/CORE/ESP_SPI_INT.OE: J2.5, SPI-ESP_CONTROL.OUT1.13 (G), SPI-LOCAL_ADD_HIGH.OUT1.13 (G), SPI-LOCAL_ADD_L.OUT1.13 (G), U1.8 (GPIO33)
/CORE/ESP_SPI_INT.PL: J2.8, SPI-LOCAL_ADDR_L.IN1.1 (SH/~LD), SPI-LOCAL_ADD_H.IN1.1 (SH/~LD), SPI-LOCAL_DATA.IN1.1 (SH/~LD), SPI-Z80_CONTROL.IN1.1 (SH/~LD), U1.9 (GPIO25)
/CORE/ESP_SPI_INT.SCK: J2.6, SPI-ESP_CONTROL.OUT1.11 (SCK), SPI-LOCAL_ADDR_L.IN1.2 (CLK), SPI-LOCAL_ADD_H.IN1.2 (CLK), SPI-LOCAL_ADD_HIGH.OUT1.11 (SCK), SPI-LOCAL_ADD_L.OUT1.11 (SCK), SPI-LOCAL_DATA.IN1.2 (CLK), SPI-LOCAL_DATA.OUT1.11 (SCK), SPI-Z80_CONTROL.IN1.2 (CLK), U1.32 (GPIO18)
/CORE/ESP_SPI_INT.STC: J2.3, SPI-ESP_CONTROL.OUT1.12 (RCK), SPI-LOCAL_ADD_HIGH.OUT1.12 (RCK), SPI-LOCAL_ADD_L.OUT1.12 (RCK), SPI-LOCAL_DATA.OUT1.12 (RCK), U1.10 (GPIO26)
/CORE/ESP_WAIT_RESET: C1.1, ESP_CONTROL_DIRECTOR_BIAS1.8, IC3.13 (CLR), U1.18 (GPIO11)
/CORE/EX_MISO: EX_SPI1.3, U1.13 (GPIO12)
/CORE/EX_MOSI: EX_SPI1.4, U1.15 (GPIO13)
/CORE/EX_SCK: EX_SPI1.2, U1.12 (GPIO14)
/CORE/EX_SS: EX_SPI1.1, U1.25 (GPIO8)
/CORE/IORQ_FILTER_BIT: IC21.12 (I0), JP1.2
/CORE/PRE_Z80_HARDLOCK: IC3.4 (PRE), IC13.3 (O)
/CORE/SD_CARD_SS: U1.24 (GPIO15), U1.38 (GPIO22)
/CORE/Z80_ADD_CONNECT: D2.2 (A), ESP_CONTROL_DIRECTOR_BIAS1.6, IC22.1 (I0)
/CORE/Z80_CONTROL.BUSACK: D12.1 (K), J1.24, J3.7, J8.10, SPI-Z80_CONTROL.IN1.5 (G)
/CORE/Z80_CONTROL.BUSRQ: D7.2 (A), J1.28, J3.5, J8.6, SPI-Z80_CONTROL.IN1.3 (E)
/CORE/Z80_CONTROL.IORQ: ESP_CONTROL_DIRECTOR1.5 (Y3), IC13.10 (I1), J1.30, J3.3, J8.4, SPI-Z80_CONTROL.IN1.13 (C)
/CORE/Z80_CONTROL.MEMRQ: ESP_CONTROL_DIRECTOR1.3 (Y4), IC19.10 (I1), J1.29, J3.4, J8.5, SPI-Z80_CONTROL.IN1.14 (D)
/CORE/Z80_CONTROL.NMI: D10.2 (A), J1.26, J3.8, J8.8, SPI-Z80_CONTROL.IN1.6 (H)
/CORE/Z80_CONTROL.RD: ESP_CONTROL_DIRECTOR1.9 (Y1), IC15.9 (I0), IC19.4 (I0), IC21.4 (I0), J1.32, J3.1, J8.2, RIO_CONTROL1.17 (A4), SPI-Z80_CONTROL.IN1.11 (A)
/CORE/Z80_CONTROL.RESET: D4.2 (A), J1.23, J8.11, JP4.1
/CORE/Z80_CONTROL.ROMCS: D9.2 (A), J1.25, J8.9
/CORE/Z80_CONTROL.WAIT: D6.1 (K), D8.2 (A), D13.2 (A), J1.27, J3.6, J8.7, SPI-Z80_CONTROL.IN1.4 (F)
/CORE/Z80_CONTROL.WR: ESP_CONTROL_DIRECTOR1.7 (Y2), IC15.4 (I0), IC19.2 (I1), IC19.12 (I0), J1.31, J3.2, J8.3, SPI-Z80_CONTROL.IN1.12 (B)
/CORE/Z80_DATA_CONNECT: D3.2 (A), ESP_CONTROL_DIRECTOR_BIAS1.7, IC21.10 (I1), IC22.12 (I0)
/ESP_IOD_CONFIG: IC4.8 (O), IC19.1 (I0), IC19.5 (I1), IC20.5 (I1), IC20.12 (I0), IC22.4 (I0)
/ESP_ROMSEL_0: RIO_CONTROL1.11 (A1), U1.23 (GPIO7)
/ESP_ROMSEL_1: RIO_CONTROL1.13 (A2), U1.22 (GPIO6)
/ESP_ROM_WR_PROTECT: IC19.13 (I1), U1.28 (GPIO4)
/PERM_Z80_IORQ: IC13.4 (I0), IC15.12 (I0), IC20.1 (I0), IC20.4 (I0), IC21.1 (I0), IC21.5 (I1), IC21.11 (O), IC22.13 (I1), RIO_DECODER1.19 (G)
/RIO/DEC14: RIO1.3 (A14), RIO_CONTROL1.9 (Y1), RIO_CONTROL1.18 (Y1), RN4.2
/RIO/DEC15: RIO1.31 (A15), RIO_CONTROL1.7 (Y2), RIO_CONTROL1.16 (Y2), RN4.3
/RIO/DEC16: IC20.6 (O), IC20.10 (I1), RIO1.2 (A16), RIO_CONTROL1.1 (G)
/RIO/DEC_CE: IC20.8 (O), RIO1.22 (~CE)
/RIO/DEC_OE: RIO1.24 (~OE), RIO_CONTROL1.3 (Y4), RIO_CONTROL1.12 (Y4), RN4.5, Z80-RIO_DATA1.1 (DIR)
/RIO/DEC_WE: RIO1.29 (~WE), RIO_CONTROL1.5 (Y3), RIO_CONTROL1.14 (Y3), RN4.4
/RIO/ESP_IOD_CONFIG+Z80_WR: IC19.3 (O), RIO_CONTROL1.6 (A3)
/RIO/RIO_CE2: R11.2, RIO1.30 (CE2)
/RIO/ROM_D0: RIO1.13 (DQ0), RIO_DECODER1.2 (A1), Z80-RIO_DATA1.18 (B1)
/RIO/ROM_D1: RIO1.14 (DQ1), RIO_DECODER1.3 (A2), Z80-RIO_DATA1.17 (B2)
/RIO/ROM_D2: RIO1.15 (DQ2), RIO_DECODER1.4 (A3), Z80-RIO_DATA1.16 (B3)
/RIO/ROM_D3: RIO1.17 (DQ3), RIO_DECODER1.5 (A4), Z80-RIO_DATA1.15 (B4)
/RIO/ROM_D4: RIO1.18 (DQ4), RIO_DECODER1.6 (A5), Z80-RIO_DATA1.14 (B5)
/RIO/ROM_D5: RIO1.19 (DQ5), RIO_DECODER1.7 (A6), Z80-RIO_DATA1.13 (B6)
/RIO/ROM_D6: RIO1.20 (DQ6), RIO_DECODER1.8 (A7), Z80-RIO_DATA1.12 (B7)
/RIO/ROM_D7: RIO1.21 (DQ7), RIO_DECODER1.9 (A8), Z80-RIO_DATA1.11 (B8)
/RIO/ROM_D_RDY: IC19.8 (O), IC20.13 (I1), RIO_CONTROL1.19 (G), Z80-RIO_DATA1.19 (G)
/RIO/ROM_WR_PROTECT+Z80_WR: IC19.11 (O), RIO_CONTROL1.15 (A3)
/RIO/Z80_A0: J1.1, J8.20, JP1.3, RIO1.12 (A0), Z80_ADDRLOW1.2 (A1)
/RIO/Z80_A1: J1.2, J8.21, RIO1.11 (A1), Z80_ADDRLOW1.3 (A2)
/RIO/Z80_A2: J1.3, J8.22, RIO1.10 (A2), Z80_ADDRLOW1.4 (A3)
/RIO/Z80_A3: J1.4, J8.23, RIO1.9 (A3), Z80_ADDRLOW1.5 (A4)
/RIO/Z80_A4: J1.5, J8.24, RIO1.8 (A4), Z80_ADDRLOW1.6 (A5)
/RIO/Z80_A5: J1.6, J8.25, RIO1.7 (A5), Z80_ADDRLOW1.7 (A6)
/RIO/Z80_A6: J1.7, J8.26, RIO1.6 (A6), Z80_ADDRLOW1.8 (A7)
/RIO/Z80_A7: J1.8, J8.27, RIO1.5 (A7), Z80_ADDRLOW1.9 (A8)
/RIO/Z80_A8: J1.33, J8.28, RIO1.27 (A8), Z80_ADDRHIGH1.2 (A1)
/RIO/Z80_A9: J1.34, J8.29, RIO1.26 (A9), Z80_ADDRHIGH1.3 (A2)
/RIO/Z80_A10: J1.35, J8.30, RIO1.23 (A10), Z80_ADDRHIGH1.4 (A3)
/RIO/Z80_A11: J1.36, J8.31, RIO1.25 (A11), Z80_ADDRHIGH1.5 (A4)
/RIO/Z80_A12: J1.37, J8.32, RIO1.4 (A12), Z80_ADDRHIGH1.6 (A5)
/RIO/Z80_A13: J1.38, J8.33, RIO1.28 (A13), Z80_ADDRHIGH1.7 (A6)
/RIO/Z80_A14: J1.39, J8.34, RIO_CONTROL1.2 (A1), Z80_ADDRHIGH1.8 (A7)
/RIO/Z80_A15: J1.40, J8.35, RIO_CONTROL1.4 (A2), Z80_ADDRHIGH1.9 (A8)
/RIO/Z80_D0: J1.9, J8.12, Z80-LOCAL_DATA1.2 (A1), Z80-RIO_DATA1.2 (A1)
/RIO/Z80_D1: J1.10, J8.13, Z80-LOCAL_DATA1.3 (A2), Z80-RIO_DATA1.3 (A2)
/RIO/Z80_D2: J1.11, J8.14, Z80-LOCAL_DATA1.4 (A3), Z80-RIO_DATA1.4 (A3)
/RIO/Z80_D3: J1.12, J8.15, Z80-LOCAL_DATA1.5 (A4), Z80-RIO_DATA1.5 (A4)
/RIO/Z80_D4: J1.13, J8.16, Z80-LOCAL_DATA1.6 (A5), Z80-RIO_DATA1.6 (A5)
/RIO/Z80_D5: J1.14, J8.17, Z80-LOCAL_DATA1.7 (A6), Z80-RIO_DATA1.7 (A6)
/RIO/Z80_D6: J1.15, J8.18, Z80-LOCAL_DATA1.8 (A7), Z80-RIO_DATA1.8 (A7)
/RIO/Z80_D7: J1.16, J8.19, Z80-LOCAL_DATA1.9 (A8), Z80-RIO_DATA1.9 (A8)
/RIO/Z80_RD+ESP_IOD_CONFIG+PERM_Z80_IORQ: IC20.3 (O), RIO_CONTROL1.8 (A4)
/WAIT_IO: IC2.9 (I), RIO_DECODER1.13 (B6)
/Z80 BUS/VCC: J1.22, J8.40
/Z80 BUS/Z80_ADD_DIR: IC22.6 (O), Z80_ADDRHIGH1.1 (DIR), Z80_ADDRLOW1.1 (DIR)
/Z80 BUS/Z80_ADD_OE: IC22.3 (O), Z80_ADDRHIGH1.19 (G), Z80_ADDRLOW1.19 (G)
/Z80 BUS/Z80_DATA_DIR: IC22.8 (O), Z80-LOCAL_DATA1.1 (DIR)
/Z80 BUS/Z80_DATA_OE: IC22.11 (O), Z80-LOCAL_DATA1.19 (G)
/Z80_HARDLOCK: IC3.5 (Q), IC6.10 (CCLR), IC7.10 (CCLR), U1.4 (GPIO39)
/Z80_HARDLOCK_RESET: D11.1 (K), IC2.5 (I), RIO_DECODER1.12 (B7)
/Z80_HARDLOCK_SET: IC2.3 (I), RIO_DECODER1.11 (B8)
GND: C1.2, C2.2, C3.2, C4.2, C5.2, CACHE1.16 (VSS), D1.2 (A), EX_SPI1.6, J1.21, J8.1, JP1.1, JP4.2, Q1.3 (E), R5.2, RIO1.16 (VSS), SPI-LOCAL_DATA.IN1.10 (SER), U1.14 (GND), U1.21 (GND), U1.34 (GND), U1.40 (GND)
unnamed: D1.1 (K), R1.1
unnamed: D4.1 (K), U1.35 (GPIO21)
unnamed: D5.1 (K), ESP_CONTROL_DIRECTOR_BIAS1.1
unnamed: D13.1 (K), IC3.8 (~Q)
unnamed: D14.1 (K), RN4.1
unnamed: D15.1 (K), LOCAL_DATA_BIAS1.1
unnamed: D16.1 (K), ESP_CONTROL_BIAS1.1
unnamed: ESP_CONTROL_DIRECTOR1.4 (A2), ESP_CONTROL_DIRECTOR1.13 (A2), IC13.11 (O)
unnamed: IC2.6 (O), IC5.2 (I1)
unnamed: IC2.8 (O), IC3.10 (PRE)
unnamed: IC2.11 (I), IC5.6 (O)
unnamed: IC2.10 (O), IC4.9 (I0)
unnamed: C2.1, IC5.1 (I0), R4.2
unnamed: IC6.9 (RCO), IC7.11 (CLK), IC7.13 (RCK)
unnamed: IC2.4 (O), IC13.1 (I0)
unnamed: IC13.8 (O), IC21.13 (I1)
unnamed: IC19.6 (O), IC20.2 (I1)
unnamed: IC20.9 (I0), IC20.11 (O)
unnamed: IC21.3 (O), IC22.2 (I1)
unnamed: IC21.6 (O), IC22.9 (I0)
unnamed: IC21.8 (O), IC22.10 (I1)
unnamed: Q1.2 (B), R2.2
unnamed: R8.1, RIO_DECODER1.1 (DIR)
unnamed: SPI-ESP_CONTROL.OUT1.9 (QH*), SPI-LOCAL_ADD_L.OUT1.14 (SER)
unnamed: SPI-ESP_CONTROL.OUT1.14 (SER), SPI-LOCAL_DATA.OUT1.9 (QH*)
unnamed: SPI-LOCAL_ADDR_L.IN1.9 (QH), SPI-LOCAL_ADD_H.IN1.10 (SER)
unnamed: SPI-LOCAL_ADDR_L.IN1.10 (SER), SPI-Z80_CONTROL.IN1.9 (QH)
unnamed: SPI-LOCAL_ADD_HIGH.OUT1.14 (SER), SPI-LOCAL_ADD_L.OUT1.9 (QH*)
unnamed: SPI-LOCAL_DATA.IN1.9 (QH), SPI-Z80_CONTROL.IN1.10 (SER)
